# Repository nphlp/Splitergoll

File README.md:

# Splitergoll keyboard

Welcome to the Splitergoll Project: a column staggered split keyboard working with the ZMK Firmware.

- `split` : A split keyboard, one part for each hand
- `ergo` : An ergonomic keyboard with a column staggered layout
- `ll` : Low latency, requires a dongle to improve battery life and Bluetooth latency

In this repository, you will find:

- The `electronic PCB design` files created with KiCad
- The `3D printable case design` files designed using Fusion 360
- The complete [ZMK firmware](https://github.com/zmkfirmware/zmk) configuration for the **Splitergoll**.

<div>
    
    <div style="display: flex; flex-direction: row; justify-content: space-between;">

    </div>
    <div style="display: flex; flex-direction: row; justify-content: space-between;">

    </div>
    
</div>

## Licenses and Inspirations

### Bluetooth wireless keyboards

Huge thanks to these guys for their beautiful documentations about ZMK Wireless keyboards:

[KLOR Documentation](https://github.com/GEIGEIGEIST/KLOR) an INCREDIBLE documentation by GEIGEIGEIST:

- Polydactyl keyboard layout
- PCB design files
- Electronic component references
- Build guide

[Aenyhm's ZMK config](https://github.com/Aenyhm/zmk-config) for:

- French key layout correspondences (Q → A, W → Z...)
- System key correspondences (Windows, MacOS...)
- Layer system for "Windows" and "MacOS" compatibility

[Eigateck's ZMK config](https://github.com/eigatech/zmk-config) for:
- His incredible [Youtube channel](https://www.youtube.com/@EIGAtech)
- The nice documentation of its keyboards

Other great resources:

- [temper](https://github.com/raeedcho/temper) by raeedcho
- [nine-nano](https://github.com/bsag/nine-nano) by bsag
- [urchin](https://github.com/duckyb/urchin) by duckyb
- [LambBT](https://github.com/johnlamb/LambBT) by johnlamb
- [Rolio46Keyboard](https://github.com/MickiusMousius/Rolio46Keyboard) by MickiusMousius
- [SofleChocWireless](https://github.com/db-ok/SofleChocWireless) by db-ok
- [KLOTZ](https://github.com/GEIGEIGEIST/KLOTZ) by GEIGEIGEIST
- [pica40](https://github.com/zzeneg/pica40) by zzeneg
- [karn-keyboard](https://github.com/robcmills/karn-keyboard) by robcmills
- [SofleKeyboard](https://github.com/josefadamcik/SofleKeyboard) by josefadamcik

### Dongle wireless keyboards

Incredible resources about ZMK keyboards dongles:

- [Aroum's Dongle Keyboard](https://github.com/aroum/zmk-enki42-dongle) based on a `SuperMini nRF52840` as a dongle.
- [Charlesmst's Dongle Keyboard](https://github.com/charlesmst/zmk-enki42-dongle) based on a `Makerdiary nRF52840 MDK Dongle` as a dongle.
- [RasmusKoit's Dongle Keyboard](https://github.com/RasmusKoit/pipar) based on a `Seeed Studio Xiao nRF52840` as a dongle.

Eigateck's ZMK config:

- [Totem Dongle](https://github.com/eigatech/zmk-config/tree/totem-dongle)
- [Corne Dongle](https://github.com/eigatech/zmk-config/tree/corne-dongle)
- [Charybdis Dongle](https://github.com/eigatech/zmk-config/tree/charybdis-dongle)

Documentation about the dongle keyboards:

- [SliceMK Docs](https://docs.slicemk.com/firmware/zmk/wireless/dongle/): a ZMK fork which inspired Aroum's Dongle Keyboard.
- [PR#2401 Dongle Keyboard](https://github.com/zmkfirmware/zmk/pull/2401): a proposition for a dongle keyboard documentation [see preview](https://deploy-preview-2401--zmk.netlify.app/docs/features/dongle).

Hardware resources about the dongle keyboards:

- [Seeed Studio Xiao BLE](https://github.com/zmkfirmware/zmk/blob/main/app/boards/arm/seeeduino_xiao_ble/seeeduino_xiao_ble.zmk.yml)
- [Nice!Nano V2](https://github.com/zmkfirmware/zmk/blob/main/app/boards/arm/nice_nano/nice_nano_v2.yaml) (or SuperMini nRF52840) for each keyboard halve.
- [Makerdiary nRF52840 Dongle](https://github.com/zmkfirmware/zephyr/blob/v3.5.0%2Bzmk-fixes/boards/arm/nrf52840_mdk_usb_dongle/nrf52840_mdk_usb_dongle.yaml)
- [Nordic nRF52840 Dongle](https://github.com/zmkfirmware/zmk/blob/main/app/boards/arm/nrf52840dk_nrf52840/nrf52840dk_nrf52840.zmk.yml) as a dongle.

## Git Branches

Classique version:
- [main](https://github.com/nansphilip/Splitergoll/tree/main) → Bluetooth wireless keyboard
- [dongle](https://github.com/nansphilip/Splitergoll/tree/dongle) → Dongle wireless keyboard

Minimalist version (to learn ZMK):
- [main (minimalist)](https://github.com/nansphilip/Splitergoll/tree/main-minimal) → Minimalist bluetooth wireless keyboard
- [dongle (minimalist)](https://github.com/nansphilip/Splitergoll/tree/dongle-minimal) → Minimalist dongle wireless keyboard

## Todo

Works:
- [x] Global configuration: Bluetooth and USB
- [x] Switches and encoders pin connections
- [x] Battery level and sleep mode
- [x] Layer inheritance and conditions
- [x] Accents, symbols, movements
- [x] Gaming compatibility
- [x] Release default shift morph behavior
- [x] Dongle mode (needs improvements...)
- [x] French layout (make sure you are using `Français (variante)` for Linux)
- [x] Windows compatibility
- [x] Linux compatibility (needs improvements...)

Testing:
- [ ] MacOS compatibility (work in progress...)

Incoming:
- [ ] Switch Bluetooth device
- [ ] Flying macro (record a macro, replay it, and repeat it)
- [ ] Sleep mode ?
- [ ] Bluetooth power ?
- [ ] Battery reporting ?
- [ ] Debouncing ?

## Improvements

- Hotswapable switches for an easier maintenance
- Led indicators for connection status (bluetooth, usb...) and battery level
- Keycap legends for each keys for a professional look

## Layout

This keyboard is compatible with `Windows` (default) and `MacOS` (soon).
It is optimized for `desktop`, `programming`, `gaming`, and `multimedia`.

Some shortcuts and modifiers may be different:

- `CTRL` key is replaced by the `command` key
- `ALT` key is replaced by the `option` key
- `WINDOWS` key is replaced by the `control` key

This keyboard works with 4 layers:

- `DEFAULT`: letters and most used punctuation
- `PRIMARY`: text editor movements, desktop management, and all programming symbols
- `SECONDARY`: accented letters, calculation symbols, and numbers
- `TERTIARY`: miscellaneous shortcuts, macros, etc.

During your reading, you will find these symbols:

- `+` means [tap dance](https://zmk.dev/docs/behaviors/tap-dance)
- `→` means [hold tap](https://zmk.dev/docs/behaviors/hold-tap)
- `or` means [shift morph tap](https://zmk.dev/docs/behaviors/mod-morph)

### Default layer

> Philosophy

The default layer contains all letters and the most frequent punctuation symbols. This main layer can be shifted to access uppercase letters and shift-morphed symbols.

The modifiers `SHIFT` key and `NUMPAD` layer can be locked (toggle → press modifier) by tap dance patterns (follow the `Lock usage` section below).
You can easily unlock them (toggle → release modifier) by a single tap on the respective keys.

> Shortcuts

#### Basic usage

- `SHIFT` to shift layer
- `L1` to layer 1
- `L2` to layer 2

#### Combo usage

- `L1` + `L2` to layer 3

#### Alternative usage

- `L1` + `L1` to layer 2
- `L2` + `L2` to layer 1

#### Lock usage

- `SHIFT` + `SHIFT` to LOCK shift layer
- `SHIFT` to UNLOCK shift layer

- `L1` + `L1` + `L1` to LOCK numpad layer
- `L1` to UNLOCK numpad layer

```keymap
┏━━━━━━━━━━━┳━━━━━━━━━━━┳━━━━━━━━━━━┳━━━━━━━━━━━┳━━━━━━━━━━━┳━━━━━━━━━━━┓   ┏━━━━━━━━━━━┳━━━━━━━━━━━┳━━━━━━━━━━━┳━━━━━━━━━━━┳━━━━━━━━━━━┳━━━━━━━━━━━┓
┃    ESC    ┃     A     ┃     Z     ┃     E     ┃     R     ┃     T     ┃   ┃     Y     ┃     U     ┃     I     ┃     O     ┃     P     ┃   BSPACE  ┃
┣━━━━━━━━━━━╋━━━━━━━━━━━╋━━━━━━━━━━━╋━━━━━━━━━━━╋━━━━━━━━━━━╋━━━━━━━━━━━┫   ┣━━━━━━━━━━━╋━━━━━━━━━━━╋━━━━━━━━━━━╋━━━━━━━━━━━╋━━━━━━━━━━━╋━━━━━━━━━━━┫
┃    TAB    ┃     Q     ┃     S     ┃     D     ┃     F     ┃     G     ┃   ┃     H     ┃     J     ┃     K     ┃     L     ┃     M     ┃    DEL    ┃
┗━━━━━━━━━━━╋━━━━━━━━━━━╋━━━━━━━━━━━╋━━━━━━━━━━━╋━━━━━━━━━━━╋━━━━━━━━━━━┫   ┣━━━━━━━━━━━╋━━━━━━━━━━━╋━━━━━━━━━━━╋━━━━━━━━━━━╋━━━━━━━━━━━╋━━━━━━━━━━━┛
            ┃     W     ┃     X     ┃     C     ┃     V     ┃     B     ┃   ┃     N     ┃  , or ?   ┃  . or !   ┃  ; or /   ┃  : or \   ┃
╭───────╮   ┗━━━━━━━━━━━┻━━━━━━━━━━━┻━━━━━━━━━━━┻━━━━━━━━━━━┻━━━━━━━━━━━┛   ┗━━━━━━━━━━━┻━━━━━━━━━━━┻━━━━━━━━━━━┻━━━━━━━━━━━┻━━━━━━━━━━━┛   ╭───────╮
│ VOL+  │ ┏━━━━━━━━━━━┓ ┏━━━━━━━━━━━┳━━━━━━━━━━━┳━━━━━━━━━━━┳━━━━━━━━━━━┓   ┏━━━━━━━━━━━┳━━━━━━━━━━━┳━━━━━━━━━━━┳━━━━━━━━━━━┓ ┏━━━━━━━━━━━┓ │ LEFT  │
│ VOL-  │ ┃ Play→Mute ┃ ┃   CTRL    ┃    ALT    ┃     L2    ┃   SPACE   ┃   ┃SHIFT+LOCK ┃     L1    ┃   ENTER   ┃    WIN    ┃ ┃ To Linux  ┃ │ RIGHT │
╰───────╯ ┗━━━━━━━━━━━┛ ┗━━━━━━━━━━━┻━━━━━━━━━━━┻━━━━━━━━━━━┻━━━━━━━━━━━┛   ┗━━━━━━━━━━━┻━━━━━━━━━━━┻━━━━━━━━━━━┻━━━━━━━━━━━┛ ┗━━━━━━━━━━━┛ ╰───────╯
```

### Primary layer

> Philosophy

The first layer is optimized for programming: directional arrows, word jump shortcuts, home and end line, and every symbol.

> Shortcuts

- `L1` + `SHIFT²` + `←, ↑, ↓ or →` to select text
- `L1` + `ALT` + `↑ or ↓` to move up/down a row
- `L1` + `ALT` + `SHIFT` + `↑ or ↓` to duplicate a row
- `L1` + `ALT` + `CTRL` + `↑ or ↓` to create multiline cursor

```keymap
┏━━━━━━━━━━━┳━━━━━━━━━━━┳━━━━━━━━━━━┳━━━━━━━━━━━┳━━━━━━━━━━━┳━━━━━━━━━━━┓   ┏━━━━━━━━━━━┳━━━━━━━━━━━┳━━━━━━━━━━━┳━━━━━━━━━━━┳━━━━━━━━━━━┳━━━━━━━━━━━┓
┃           ┃Del desktop┃   HOME    ┃Show desktp┃    END    ┃New desktop┃   ┃     "     ┃     (     ┃     )     ┃     [     ┃     ]     ┃           ┃
┣━━━━━━━━━━━╋━━━━━━━━━━━╋━━━━━━━━━━━╋━━━━━━━━━━━╋━━━━━━━━━━━╋━━━━━━━━━━━┫   ┣━━━━━━━━━━━╋━━━━━━━━━━━╋━━━━━━━━━━━╋━━━━━━━━━━━╋━━━━━━━━━━━╋━━━━━━━━━━━┫
┃           ┃Left desktp┃     ←     ┃     ↑     ┃     →     ┃Right deskp┃   ┃     '     ┃     {     ┃     }     ┃     <     ┃     >     ┃           ┃
┗━━━━━━━━━━━╋━━━━━━━━━━━╋━━━━━━━━━━━╋━━━━━━━━━━━╋━━━━━━━━━━━╋━━━━━━━━━━━┫   ┣━━━━━━━━━━━╋━━━━━━━━━━━╋━━━━━━━━━━━╋━━━━━━━━━━━╋━━━━━━━━━━━╋━━━━━━━━━━━┛
            ┃           ┃  CTRL ←   ┃     ↓     ┃   CTRL →  ┃           ┃   ┃     `     ┃     #     ┃     &     ┃     |     ┃     @     ┃
╭───────╮   ┗━━━━━━━━━━━┻━━━━━━━━━━━┻━━━━━━━━━━━┻━━━━━━━━━━━┻━━━━━━━━━━━┛   ┗━━━━━━━━━━━┻━━━━━━━━━━━┻━━━━━━━━━━━┻━━━━━━━━━━━┻━━━━━━━━━━━┛   ╭───────╮
│ LEFT  │ ┏━━━━━━━━━━━┓ ┏━━━━━━━━━━━┳━━━━━━━━━━━┳━━━━━━━━━━━┳━━━━━━━━━━━┓   ┏━━━━━━━━━━━┳━━━━━━━━━━━┳━━━━━━━━━━━┳━━━━━━━━━━━┓ ┏━━━━━━━━━━━┓ │ UP    │
│ RIGHT │ ┃           ┃ ┃           ┃           ┃           ┃   SHIFT²  ┃   ┃   SHIFT   ┃     L1    ┃           ┃           ┃ ┃ "Windows" ┃ │ DOWN  │
╰───────╯ ┗━━━━━━━━━━━┛ ┗━━━━━━━━━━━┻━━━━━━━━━━━┻━━━━━━━━━━━┻━━━━━━━━━━━┛   ┗━━━━━━━━━━━┻━━━━━━━━━━━┻━━━━━━━━━━━┻━━━━━━━━━━━┛ ┗━━━━━━━━━━━┛ ╰───────╯
```

### Secondary layer

> Philosophy

The second layer contains all French accents on the left side, and a numpad with calculation symbols on the right side.

Accented letters are positioned by frequency and sorted by letter and accent.
You have to single, double, or triple click to reach even keys.

> Shortcuts

Common use case:

- `L2` + `CTRL` + `+` to zoom in
- `L2` + `CTRL` + `-` to zoom out
- `L2` + `SPACE` to space, useful with numpad

Left hand on keyboard, and right hand on mouse:

- `L2` + `CTRL` + `/` to comment/uncomment (add it to VSCode settings)
- `L2` + `ENTER` to return
- `L2` + `BSPACE` to backspace
- `L2` + `DEL` to delete

```keymap
┏━━━━━━━━━━━┳━━━━━━━━━━━┳━━━━━━━━━━━┳━━━━━━━━━━━┳━━━━━━━━━━━┳━━━━━━━━━━━┓   ┏━━━━━━━━━━━┳━━━━━━━━━━━┳━━━━━━━━━━━┳━━━━━━━━━━━┳━━━━━━━━━━━┳━━━━━━━━━━━┓
┃   BSPACE* ┃   œ + Œ   ┃ ° + ² + ³ ┃     _     ┃     -     ┃     +     ┃   ┃     =     ┃     7     ┃     8     ┃     9     ┃   € + £   ┃           ┃
┣━━━━━━━━━━━╋━━━━━━━━━━━╋━━━━━━━━━━━╋━━━━━━━━━━━╋━━━━━━━━━━━╋━━━━━━━━━━━┫   ┣━━━━━━━━━━━╋━━━━━━━━━━━╋━━━━━━━━━━━╋━━━━━━━━━━━╋━━━━━━━━━━━╋━━━━━━━━━━━┫
┃    DEL*   ┃   ô + Ô   ┃   é + É   ┃   ê + Ê   ┃   è + ë   ┃     *     ┃   ┃     0     ┃     4     ┃     5     ┃     6     ┃     $     ┃           ┃
┗━━━━━━━━━━━╋━━━━━━━━━━━╋━━━━━━━━━━━╋━━━━━━━━━━━╋━━━━━━━━━━━╋━━━━━━━━━━━┫   ┣━━━━━━━━━━━╋━━━━━━━━━━━╋━━━━━━━━━━━╋━━━━━━━━━━━╋━━━━━━━━━━━╋━━━━━━━━━━━┛
            ┃   î + ï   ┃ ù + û + μ ┃   ç + Ç   ┃ à + â + À ┃     /     ┃   ┃     .     ┃     1     ┃     2     ┃     3     ┃     %     ┃
╭───────╮   ┗━━━━━━━━━━━┻━━━━━━━━━━━┻━━━━━━━━━━━┻━━━━━━━━━━━┻━━━━━━━━━━━┛   ┗━━━━━━━━━━━┻━━━━━━━━━━━┻━━━━━━━━━━━┻━━━━━━━━━━━┻━━━━━━━━━━━┛   ╭───────╮
│ LEFT  │ ┏━━━━━━━━━━━┓ ┏━━━━━━━━━━━┳━━━━━━━━━━━┳━━━━━━━━━━━┳━━━━━━━━━━━┓   ┏━━━━━━━━━━━┳━━━━━━━━━━━┳━━━━━━━━━━━┳━━━━━━━━━━━┓ ┏━━━━━━━━━━━┓ │ UP    │
│ RIGHT │ ┃           ┃ ┃           ┃           ┃     L2    ┃   ENTER   ┃   ┃   SPACE   ┃           ┃           ┃           ┃ ┃           ┃ │ DOWN  │
╰───────╯ ┗━━━━━━━━━━━┛ ┗━━━━━━━━━━━┻━━━━━━━━━━━┻━━━━━━━━━━━┻━━━━━━━━━━━┛   ┗━━━━━━━━━━━┻━━━━━━━━━━━┻━━━━━━━━━━━┻━━━━━━━━━━━┛ ┗━━━━━━━━━━━┛ ╰───────╯
```

### Tertiary layer

> Philosophy

The third layer is used for complex shortcuts, arrow characters, and still contains empty keys that are waiting to find a utility.

```keymap
┏━━━━━━━━━━━┳━━━━━━━━━━━┳━━━━━━━━━━━┳━━━━━━━━━━━┳━━━━━━━━━━━┳━━━━━━━━━━━┓   ┏━━━━━━━━━━━┳━━━━━━━━━━━┳━━━━━━━━━━━┳━━━━━━━━━━━┳━━━━━━━━━━━┳━━━━━━━━━━━┓
┃    F1     ┃    F2     ┃    F3     ┃    F4     ┃    F5     ┃    F6     ┃   ┃    F7     ┃    F8     ┃    F9     ┃    F10    ┃    F11    ┃    F12    ┃
┣━━━━━━━━━━━╋━━━━━━━━━━━╋━━━━━━━━━━━╋━━━━━━━━━━━╋━━━━━━━━━━━╋━━━━━━━━━━━┫   ┣━━━━━━━━━━━╋━━━━━━━━━━━╋━━━━━━━━━━━╋━━━━━━━━━━━╋━━━━━━━━━━━╋━━━━━━━━━━━┫
┃   Reset   ┃           ┃     ←     ┃     ↑     ┃     →     ┃Rec Screen ┃   ┃           ┃           ┃           ┃           ┃           ┃ ALT + F4  ┃
┗━━━━━━━━━━━╋━━━━━━━━━━━╋━━━━━━━━━━━╋━━━━━━━━━━━╋━━━━━━━━━━━╋━━━━━━━━━━━┫   ┣━━━━━━━━━━━╋━━━━━━━━━━━╋━━━━━━━━━━━╋━━━━━━━━━━━╋━━━━━━━━━━━╋━━━━━━━━━━━┛
            ┃           ┃           ┃     ↓     ┃           ┃Print Scree┃   ┃           ┃           ┃           ┃           ┃           ┃
╭───────╮   ┗━━━━━━━━━━━┻━━━━━━━━━━━┻━━━━━━━━━━━┻━━━━━━━━━━━┻━━━━━━━━━━━┛   ┗━━━━━━━━━━━┻━━━━━━━━━━━┻━━━━━━━━━━━┻━━━━━━━━━━━┻━━━━━━━━━━━┛   ╭───────╮
│ UP    │ ┏━━━━━━━━━━━┓ ┏━━━━━━━━━━━┳━━━━━━━━━━━┳━━━━━━━━━━━┳━━━━━━━━━━━┓   ┏━━━━━━━━━━━┳━━━━━━━━━━━┳━━━━━━━━━━━┳━━━━━━━━━━━┓ ┏━━━━━━━━━━━┓ │ LEFT  │
│ DOWN  │ ┃ Bootloader┃ ┃   CTRL    ┃    ALT    ┃     L3    ┃           ┃   ┃   SHIFT   ┃     L3    ┃           ┃   To L8   ┃ ┃Del BT link┃ │ RIGHT │
╰───────╯ ┗━━━━━━━━━━━┛ ┗━━━━━━━━━━━┻━━━━━━━━━━━┻━━━━━━━━━━━┻━━━━━━━━━━━┛   ┗━━━━━━━━━━━┻━━━━━━━━━━━┻━━━━━━━━━━━┻━━━━━━━━━━━┛ ┗━━━━━━━━━━━┛ ╰───────╯
```

### Numpad layer

> Philosophy

The numpad layer is useful for editing a calculation sheet, conception entering values, etc...
This layer is a hybrid between the main layer and the secondary layer: you have every number and calculation symbols, but you have also arrows, and essentials keys for the common shortcuts (copy, paste, undo, redo, etc).

```keymap
┏━━━━━━━━━━━┳━━━━━━━━━━━┳━━━━━━━━━━━┳━━━━━━━━━━━┳━━━━━━━━━━━┳━━━━━━━━━━━┓   ┏━━━━━━━━━━━┳━━━━━━━━━━━┳━━━━━━━━━━━┳━━━━━━━━━━━┳━━━━━━━━━━━┳━━━━━━━━━━━┓
┃    ESC    ┃     A     ┃     Z     ┃     ↑     ┃     -     ┃     +     ┃   ┃     =     ┃     7     ┃     8     ┃     9     ┃   € + £   ┃   BSPACE  ┃
┣━━━━━━━━━━━╋━━━━━━━━━━━╋━━━━━━━━━━━╋━━━━━━━━━━━╋━━━━━━━━━━━╋━━━━━━━━━━━┫   ┣━━━━━━━━━━━╋━━━━━━━━━━━╋━━━━━━━━━━━╋━━━━━━━━━━━╋━━━━━━━━━━━╋━━━━━━━━━━━┫
┃    TAB    ┃     Y     ┃     ←     ┃     ↓     ┃     →     ┃     *     ┃   ┃     0     ┃     4     ┃     5     ┃     6     ┃     $     ┃    DEL    ┃
┗━━━━━━━━━━━╋━━━━━━━━━━━╋━━━━━━━━━━━╋━━━━━━━━━━━╋━━━━━━━━━━━╋━━━━━━━━━━━┫   ┣━━━━━━━━━━━╋━━━━━━━━━━━╋━━━━━━━━━━━╋━━━━━━━━━━━╋━━━━━━━━━━━╋━━━━━━━━━━━┛
            ┃           ┃     X     ┃     C     ┃     V     ┃     /     ┃   ┃     .     ┃     1     ┃     2     ┃     3     ┃     %     ┃
╭───────╮   ┗━━━━━━━━━━━┻━━━━━━━━━━━┻━━━━━━━━━━━┻━━━━━━━━━━━┻━━━━━━━━━━━┛   ┗━━━━━━━━━━━┻━━━━━━━━━━━┻━━━━━━━━━━━┻━━━━━━━━━━━┻━━━━━━━━━━━┛   ╭───────╮
│ LEFT  │ ┏━━━━━━━━━━━┓ ┏━━━━━━━━━━━┳━━━━━━━━━━━┳━━━━━━━━━━━┳━━━━━━━━━━━┓   ┏━━━━━━━━━━━┳━━━━━━━━━━━┳━━━━━━━━━━━┳━━━━━━━━━━━┓ ┏━━━━━━━━━━━┓ │ UP    │
│ RIGHT │ ┃           ┃ ┃   CTRL    ┃           ┃   BSPACE  ┃    DEL    ┃   ┃   SPACE   ┃           ┃   ENTER   ┃    WIN    ┃ ┃           ┃ │ DOWN  │
╰───────╯ ┗━━━━━━━━━━━┛ ┗━━━━━━━━━━━┻━━━━━━━━━━━┻━━━━━━━━━━━┻━━━━━━━━━━━┛   ┗━━━━━━━━━━━┻━━━━━━━━━━━┻━━━━━━━━━━━┻━━━━━━━━━━━┛ ┗━━━━━━━━━━━┛ ╰───────╯
```

### Gaming layer

> Philosophy

The gaming layer must be designed to prevent accidental clicks: wrong clicks, unwanted shortcuts, etc.
However, it should still be comprehensive enough to facilitate easy communication in gaming chats.

The `ESC` key is too close to the other frequently used keys. The `ESC` key needs to be held for 200ms to be pressed.

The `CTRL`, `ALT`, and `L3` keys are replaced with non-modifier keys.

```keymap
┏━━━━━━━━━━━┳━━━━━━━━━━━┳━━━━━━━━━━━┳━━━━━━━━━━━┳━━━━━━━━━━━┳━━━━━━━━━━━┓   ┏━━━━━━━━━━━┳━━━━━━━━━━━┳━━━━━━━━━━━┳━━━━━━━━━━━┳━━━━━━━━━━━┳━━━━━━━━━━━┓
┃ (Tab)→ESC ┃     A     ┃     Z     ┃     E     ┃     R     ┃     T     ┃   ┃     Y     ┃     U     ┃     I     ┃     O     ┃     P     ┃   BSPACE  ┃
┣━━━━━━━━━━━╋━━━━━━━━━━━╋━━━━━━━━━━━╋━━━━━━━━━━━╋━━━━━━━━━━━╋━━━━━━━━━━━┫   ┣━━━━━━━━━━━╋━━━━━━━━━━━╋━━━━━━━━━━━╋━━━━━━━━━━━╋━━━━━━━━━━━╋━━━━━━━━━━━┫
┃    Tab    ┃     Q     ┃     S     ┃     D     ┃     F     ┃     G     ┃   ┃     H     ┃     J     ┃     K     ┃     L     ┃     M     ┃    DEL    ┃
┗━━━━━━━━━━━╋━━━━━━━━━━━╋━━━━━━━━━━━╋━━━━━━━━━━━╋━━━━━━━━━━━╋━━━━━━━━━━━┫   ┣━━━━━━━━━━━╋━━━━━━━━━━━╋━━━━━━━━━━━╋━━━━━━━━━━━╋━━━━━━━━━━━╋━━━━━━━━━━━┛
            ┃     W     ┃     X     ┃     C     ┃     V     ┃     B     ┃   ┃     N     ┃  , or ?   ┃  . or !   ┃  ; or /   ┃  : or \   ┃
╭───────╮   ┗━━━━━━━━━━━┻━━━━━━━━━━━┻━━━━━━━━━━━┻━━━━━━━━━━━┻━━━━━━━━━━━┛   ┗━━━━━━━━━━━┻━━━━━━━━━━━┻━━━━━━━━━━━┻━━━━━━━━━━━┻━━━━━━━━━━━┛   ╭───────╮
│ VOL+  │ ┏━━━━━━━━━━━┓ ┏━━━━━━━━━━━┳━━━━━━━━━━━┳━━━━━━━━━━━┳━━━━━━━━━━━┓   ┏━━━━━━━━━━━┳━━━━━━━━━━━┳━━━━━━━━━━━┳━━━━━━━━━━━┓ ┏━━━━━━━━━━━┓ │ VOL+  │
│ VOL-  │ ┃   To L0   ┃ ┃     +     ┃     -     ┃     '     ┃   SPACE   ┃   ┃   SHIFT   ┃     L9    ┃   ENTER   ┃    WIN    ┃ ┃           ┃ │ VOL-  │
╰───────╯ ┗━━━━━━━━━━━┛ ┗━━━━━━━━━━━┻━━━━━━━━━━━┻━━━━━━━━━━━┻━━━━━━━━━━━┛   ┗━━━━━━━━━━━┻━━━━━━━━━━━┻━━━━━━━━━━━┻━━━━━━━━━━━┛ ┗━━━━━━━━━━━┛ ╰───────╯
```

### Gaming layer 2

> NVidia Shortcuts

- `NV_Scrn` to take screenshot
- `NV_FPS` to show performance panel
- `NV_Swth` to toggle performance panel content
- `NV_Strt` to start recording
- `NV_Save` to save recording
- `NV_Dsh` to show dashboard

```keymap
┏━━━━━━━━━━━┳━━━━━━━━━━━┳━━━━━━━━━━━┳━━━━━━━━━━━┳━━━━━━━━━━━┳━━━━━━━━━━━┓   ┏━━━━━━━━━━━┳━━━━━━━━━━━┳━━━━━━━━━━━┳━━━━━━━━━━━┳━━━━━━━━━━━┳━━━━━━━━━━━┓
┃           ┃           ┃           ┃           ┃           ┃           ┃   ┃     "     ┃NV ScrenSht┃           ┃           ┃           ┃           ┃
┣━━━━━━━━━━━╋━━━━━━━━━━━╋━━━━━━━━━━━╋━━━━━━━━━━━╋━━━━━━━━━━━╋━━━━━━━━━━━┫   ┣━━━━━━━━━━━╋━━━━━━━━━━━╋━━━━━━━━━━━╋━━━━━━━━━━━╋━━━━━━━━━━━╋━━━━━━━━━━━┫
┃           ┃           ┃           ┃           ┃           ┃           ┃   ┃     '     ┃NV Save Rec┃NV StartRec┃           ┃           ┃           ┃
┗━━━━━━━━━━━╋━━━━━━━━━━━╋━━━━━━━━━━━╋━━━━━━━━━━━╋━━━━━━━━━━━╋━━━━━━━━━━━┫   ┣━━━━━━━━━━━╋━━━━━━━━━━━╋━━━━━━━━━━━╋━━━━━━━━━━━╋━━━━━━━━━━━╋━━━━━━━━━━━┛
            ┃           ┃           ┃           ┃           ┃           ┃         `     ┃NV Dashbrd ┃  NV FPS   ┃ NV Rotate ┃           ┃
╭───────╮   ┗━━━━━━━━━━━┻━━━━━━━━━━━┻━━━━━━━━━━━┻━━━━━━━━━━━┻━━━━━━━━━━━┛   ┗━━━━━━━━━━━┻━━━━━━━━━━━┻━━━━━━━━━━━┻━━━━━━━━━━━┻━━━━━━━━━━━┛   ╭───────╮
│ VOL+  │ ┏━━━━━━━━━━━┓ ┏━━━━━━━━━━━┳━━━━━━━━━━━┳━━━━━━━━━━━┳━━━━━━━━━━━┓   ┏━━━━━━━━━━━┳━━━━━━━━━━━┳━━━━━━━━━━━┳━━━━━━━━━━━┓ ┏━━━━━━━━━━━┓ │ VOL+  │
│ VOL-  │ ┃           ┃ ┃   CTRL    ┃    ALT    ┃           ┃           ┃   ┃           ┃    L10    ┃           ┃           ┃ ┃           ┃ │ VOL-  │
╰───────╯ ┗━━━━━━━━━━━┛ ┗━━━━━━━━━━━┻━━━━━━━━━━━┻━━━━━━━━━━━┻━━━━━━━━━━━┛   ┗━━━━━━━━━━━┻━━━━━━━━━━━┻━━━━━━━━━━━┻━━━━━━━━━━━┛ ┗━━━━━━━━━━━┛ ╰───────╯
```

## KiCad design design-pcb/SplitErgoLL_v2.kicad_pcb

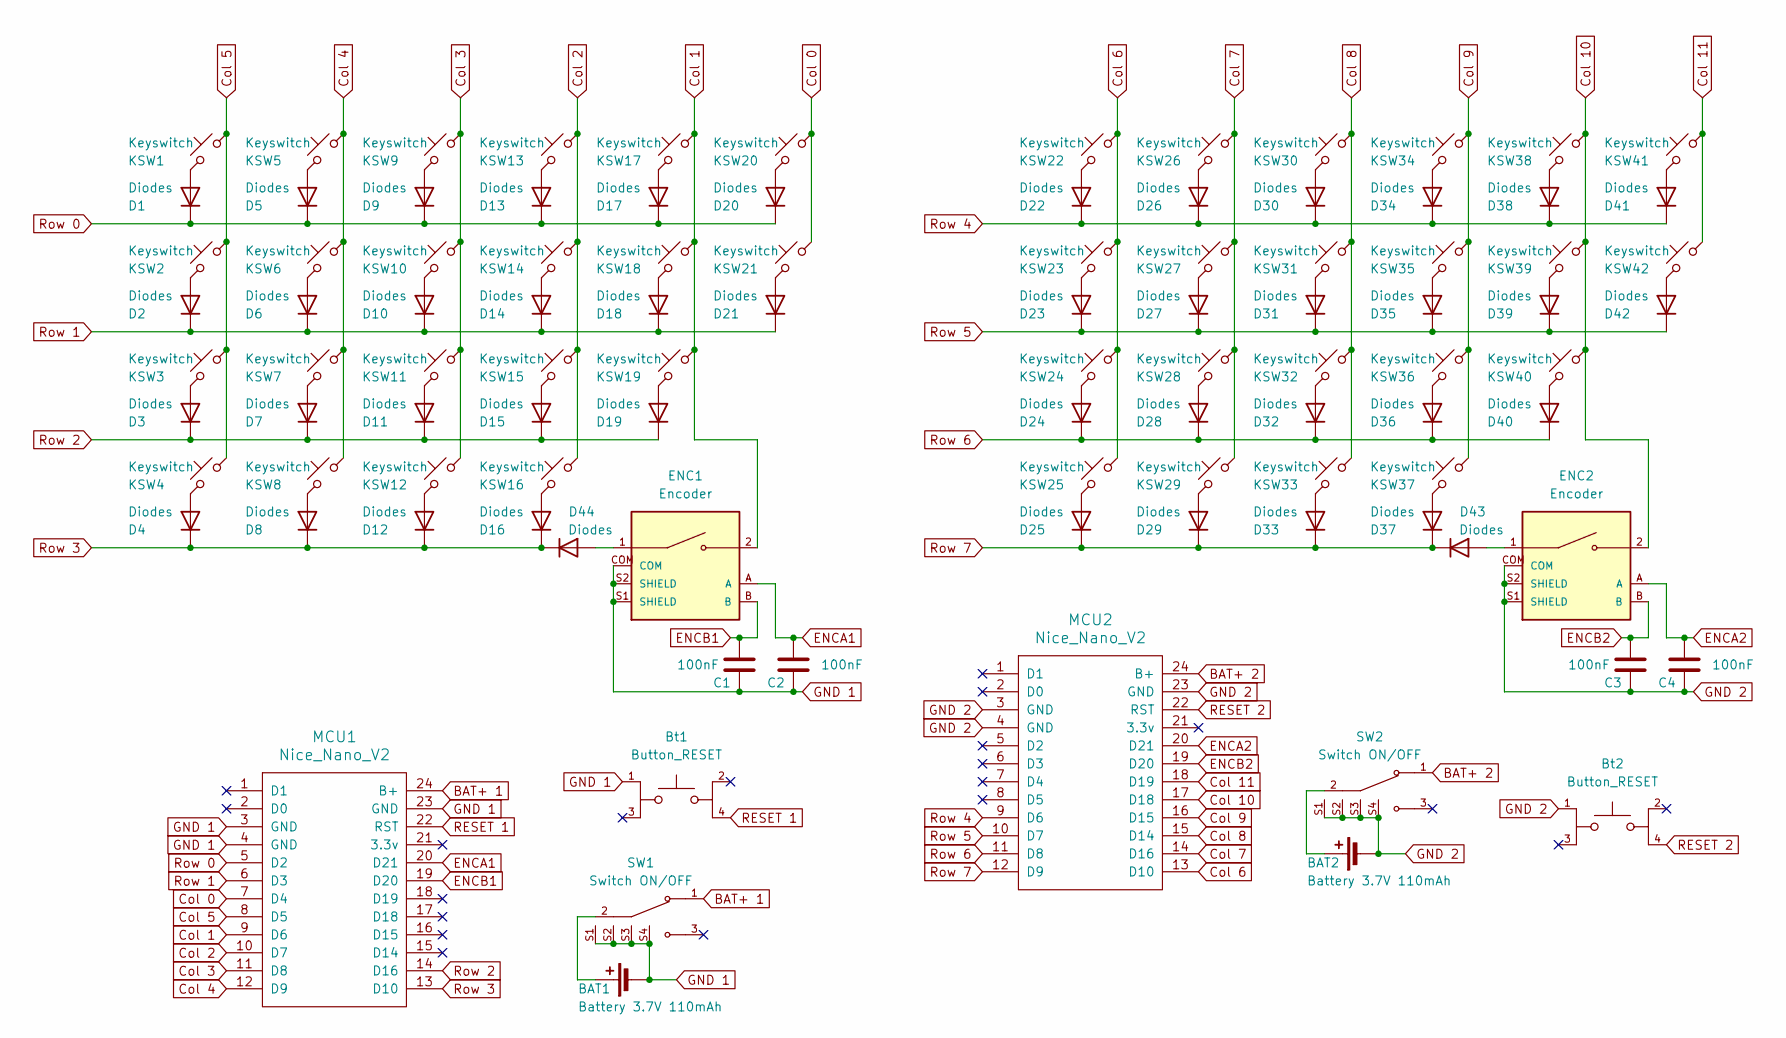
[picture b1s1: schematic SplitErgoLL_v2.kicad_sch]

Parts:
BAT1, BAT2: Battery 3.7V 110mAh; Battery_PINs
Bt1, Bt2: Button_RESET; PARTREV A
C1, C2, C3, C4: 100nF; Capacitor_SMD
D1, D2, D3, D4, D5, D6, D7, D8, D9, D10, D11, D12, D13, D14, D15, D16, D17, D18, D19, D20, D21, D22, D23, D24, D25, D26, D27, D28, D29, D30, D31, D32, D33, D34, D35, D36, D37, D38, D39, D40, D41, D42, D43, D44: Diodes; Diode_SMD
ENC1, ENC2: Encoder; PARTREV Rev. 09/19
KSW1, KSW2, KSW3, KSW4, KSW5, KSW6, KSW7, KSW8, KSW9, KSW10, KSW11, KSW12, KSW13, KSW14, KSW15, KSW16, KSW17, KSW18, KSW19, KSW20, KSW21, KSW22, KSW23, KSW24, KSW25, KSW26, KSW27, KSW28, KSW29, KSW30, KSW31, KSW32, KSW33, KSW34, KSW35, KSW36, KSW37, KSW38, KSW39, KSW40, KSW41, KSW42: Keyswitch; Keyswitch_MX
MCU1, MCU2: Nice_Nano_V2; Nice_Nano_v2
SW1, SW2: Switch ON/OFF; Switch_ON_OFF; PARTREV A

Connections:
BAT+ 1: MCU1.24 (B+), SW1.1
BAT+ 2: MCU2.24 (B+), SW2.1
Col 0: KSW1.2, KSW2.2, KSW3.2, KSW4.2, MCU1.8 (D5)
Col 1: KSW5.2, KSW6.2, KSW7.2, KSW8.2, MCU1.12 (D9)
Col 2: KSW9.2, KSW10.2, KSW11.2, KSW12.2, MCU1.11 (D8)
Col 3: KSW13.2, KSW14.2, KSW15.2, KSW16.2, MCU1.10 (D7)
Col 4: ENC1.2, KSW17.2, KSW18.2, KSW19.2, MCU1.9 (D6)
Col 5: KSW20.2, KSW21.2, MCU1.7 (D4)
Col 6: KSW22.2, KSW23.2, KSW24.2, KSW25.2, MCU2.13 (D10)
Col 7: KSW26.2, KSW27.2, KSW28.2, KSW29.2, MCU2.14 (D16)
Col 8: KSW30.2, KSW31.2, KSW32.2, KSW33.2, MCU2.15 (D14)
Col 9: KSW34.2, KSW35.2, KSW36.2, KSW37.2, MCU2.16 (D15)
Col 10: ENC2.2, KSW38.2, KSW39.2, KSW40.2, MCU2.17 (D18)
Col 11: KSW41.2, KSW42.2, MCU2.18 (D19)
ENCA1: C2.1, ENC1.A, MCU1.20 (D21)
ENCA2: C4.1, ENC2.A, MCU2.20 (D21)
ENCB1: C1.1, ENC1.B, MCU1.19 (D20)
ENCB2: C3.1, ENC2.B, MCU2.19 (D20)
GND 1: BAT1.2 (-), Bt1.1, C1.2, C2.2, ENC1.COM, ENC1.S1 (SHIELD), ENC1.S2 (SHIELD), MCU1.3 (GND), MCU1.4 (GND), MCU1.23 (GND), SW1.S1, SW1.S2, SW1.S3, SW1.S4; also elsewhere on the board
GND 2: BAT2.2 (-), Bt2.1, C3.2, C4.2, ENC2.COM, ENC2.S1 (SHIELD), ENC2.S2 (SHIELD), MCU2.3 (GND), MCU2.4 (GND), MCU2.23 (GND), SW2.S1, SW2.S2, SW2.S3, SW2.S4; also elsewhere on the board
unnamed 20: BAT1.1 (+), SW1.2; also elsewhere on the board
unnamed 21: BAT2.1 (+), SW2.2; also elsewhere on the board
unnamed: D1.2 (A), KSW1.1
unnamed: D2.2 (A), KSW2.1
unnamed: D3.2 (A), KSW3.1
unnamed: D4.2 (A), KSW4.1
unnamed: D5.2 (A), KSW5.1
unnamed: D6.2 (A), KSW6.1
unnamed: D7.2 (A), KSW7.1
unnamed: D8.2 (A), KSW8.1
unnamed: D9.2 (A), KSW9.1
unnamed: D10.2 (A), KSW10.1
unnamed: D11.2 (A), KSW11.1
unnamed: D12.2 (A), KSW12.1
unnamed: D13.2 (A), KSW13.1
unnamed: D14.2 (A), KSW14.1
unnamed: D15.2 (A), KSW15.1
unnamed: D16.2 (A), KSW16.1
unnamed: D17.2 (A), KSW17.1
unnamed: D18.2 (A), KSW18.1
unnamed: D19.2 (A), KSW19.1
unnamed: D20.2 (A), KSW20.1
unnamed: D21.2 (A), KSW21.1
unnamed: D22.2 (A), KSW22.1
unnamed: D23.2 (A), KSW23.1
unnamed: D24.2 (A), KSW24.1
unnamed: D25.2 (A), KSW25.1
unnamed: D26.2 (A), KSW26.1
unnamed: D27.2 (A), KSW27.1
unnamed: D28.2 (A), KSW28.1
unnamed: D29.2 (A), KSW29.1
unnamed: D30.2 (A), KSW30.1
unnamed: D31.2 (A), KSW31.1
unnamed: D32.2 (A), KSW32.1
unnamed: D33.2 (A), KSW33.1
unnamed: D34.2 (A), KSW34.1
unnamed: D35.2 (A), KSW35.1
unnamed: D36.2 (A), KSW36.1
unnamed: D37.2 (A), KSW37.1
unnamed: D38.2 (A), KSW38.1
unnamed: D39.2 (A), KSW39.1
unnamed: D40.2 (A), KSW40.1
unnamed: D41.2 (A), KSW41.1
unnamed: D42.2 (A), KSW42.1
unnamed: D43.2 (A), ENC2.1
unnamed: D44.2 (A), ENC1.1
RESET 1: Bt1.4, MCU1.22 (RST)
RESET 2: Bt2.4, MCU2.22 (RST)
Row 0: D1.1 (K), D5.1 (K), D9.1 (K), D13.1 (K), D17.1 (K), D20.1 (K), MCU1.5 (D2)
Row 1: D2.1 (K), D6.1 (K), D10.1 (K), D14.1 (K), D18.1 (K), D21.1 (K), MCU1.6 (D3)
Row 2: D3.1 (K), D7.1 (K), D11.1 (K), D15.1 (K), D19.1 (K), MCU1.14 (D16)
Row 3: D4.1 (K), D8.1 (K), D12.1 (K), D16.1 (K), D44.1 (K), MCU1.13 (D10)
Row 4: D22.1 (K), D26.1 (K), D30.1 (K), D34.1 (K), D38.1 (K), D41.1 (K), MCU2.9 (D6)
Row 5: D23.1 (K), D27.1 (K), D31.1 (K), D35.1 (K), D39.1 (K), D42.1 (K), MCU2.10 (D7)
Row 6: D24.1 (K), D28.1 (K), D32.1 (K), D36.1 (K), D40.1 (K), MCU2.11 (D8)
Row 7: D25.1 (K), D29.1 (K), D33.1 (K), D37.1 (K), D43.1 (K), MCU2.12 (D9)

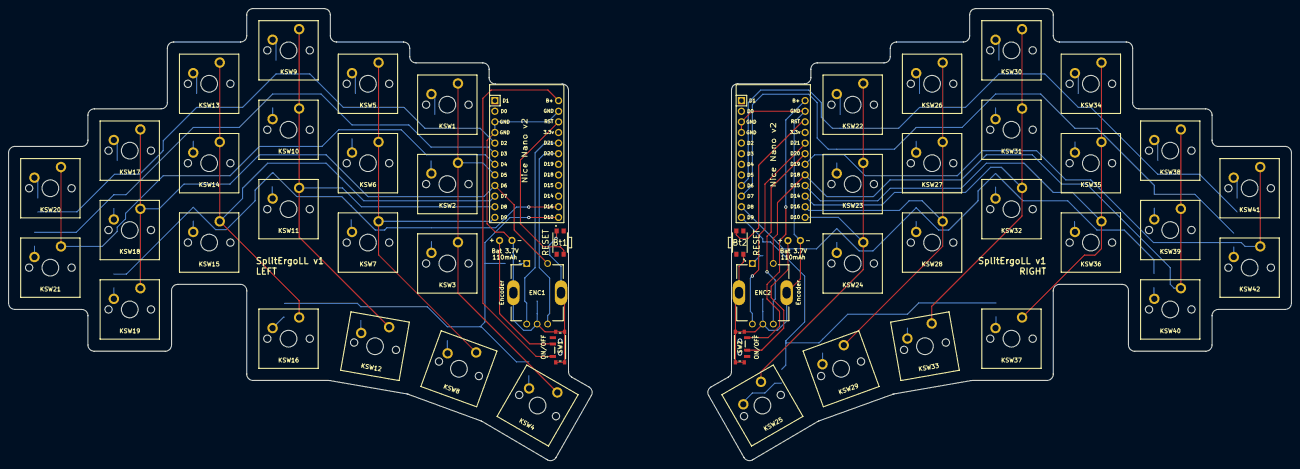
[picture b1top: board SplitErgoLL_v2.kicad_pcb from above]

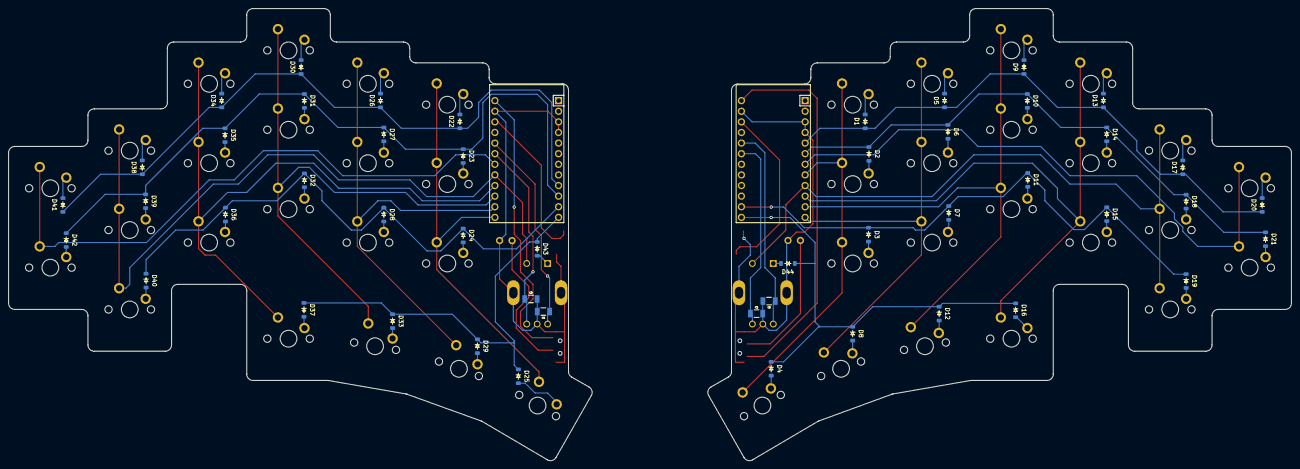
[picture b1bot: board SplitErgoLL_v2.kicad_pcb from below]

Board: 2 copper layers, 307.0 x 108.2 mm, 100 parts (48 on the bottom side), 76 nets.

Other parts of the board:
Bat 3.7V, Bat 3.7V#2: 110mAh; Battery_PINs

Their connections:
GND 1: Bat 3.7V#2.2 (-); also elsewhere on the board
GND 2: Bat 3.7V.2 (-); also elsewhere on the board
unnamed 20: Bat 3.7V#2.1 (+); also elsewhere on the board
unnamed 21: Bat 3.7V.1 (+); also elsewhere on the board
